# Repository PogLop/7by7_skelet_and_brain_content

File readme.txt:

in an unfinished state
wait for a few months 
please

thanks, 
sincerely,

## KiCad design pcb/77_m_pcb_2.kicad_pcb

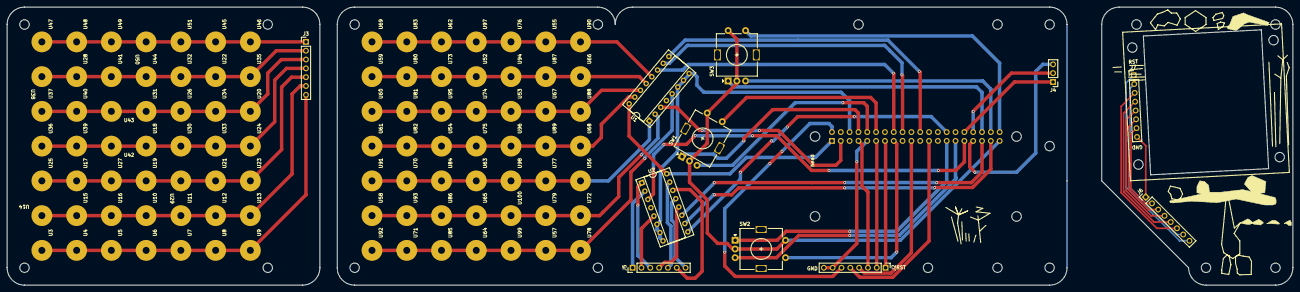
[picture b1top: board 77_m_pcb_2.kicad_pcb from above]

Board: 2 copper layers, 370.0 x 80.0 mm, 113 parts (0 on the bottom side), 59 nets.

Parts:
B1, B2, B3: Board
J1: Raspberry_Pi_2_3; Raspberry_Pi_Zero_Socketed_THT_FaceDown_MountingHoles
J2: Conn_01x08_Pin_nokia; PinHeader_1x08_P2.54mm_Vertical
J3, J5: Conn_01x07_Pin; PinHeader_1x07_P2.54mm_Vertical
J4: Conn_01x03_Pin; PinHeader_1x03_P2.54mm_Vertical
J6: Conn_01x08_Pin_nokia_balkon; PinHeader_1x08_P2.54mm_Vertical
J7: Conn_01x08_Pin_nokia_balkon_blizko; PinHeader_1x08_P2.54mm_Vertical
SW1, SW2, SW3: RotaryEncoder_Switch; RotaryEncoder_Alps_EC11E-Switch_Vertical_H20mm
U1, U2: 74HC4051; DIP-16_W7.62mm_Socket
U3, U4, U5, U6, U7, U8, U9, U10, U11, U12, U13, U14, U15, U16, U17, U18, U19, U20, U21, U22, U23, U24, U25, U26, U27, U28, U29, U30, U31, U32, U33, U34, U35, U36, U37, U38, U39, U40, U41, U42, U43, U44, U45, U46, U47, U48, U49, U50, U51, U52, U53, U54, U55, U56, U57, U58, U59, U60, U61, U62, U63, U64, U65, U66, U67, U68, U69, U70, U71, U72, U73, U74, U75, U76, U77, U78, U79, U80, U81, U82, U83, U84, U85, U86, U87, U88, U89, U90, U91, U92, U93, U94, U95, U96, U97, U98, U99, U100: 1x1_matrix_pin

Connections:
COM1: J1.3 (SDA/GPIO2), U1.3 (A)
COM2: J1.31 (GCLK2/GPIO6), U2.3 (A)
GND_PNUKY_ROT: J1.39 (GND), SW1.C, SW1.S2, SW2.C, SW2.S2, SW3.C, SW3.S2
KNOFL_A: J1.12 (GPIO18/PWM0), SW1.S1
KNOFL_B: J1.15 (GPIO22), SW2.S1
KNOFL_C: J1.40 (GPIO21/SCLK1), SW3.S1
NOK_BL: J1.9 (GND), J2.7, J2.8
NOK_CE: J1.11 (GPIO17), J2.2
NOK_CLK: J1.23 (SCLK0/GPIO11), J2.5
NOK_DC: J1.7 (GCLK0/GPIO4), J2.3
NOK_DIN: J1.19 (MOSI0/GPIO10), J2.4
NOK_RST: J1.13 (GPIO27), J2.1
NOK_VCC: J1.2 (5V), J2.6
unnamed: J3.1, U45.1, U46.1, U47.1, U48.1, U49.1, U50.1, U51.1
unnamed: J3.2, U22.1, U28.1, U32.1, U35.1, U38.1, U41.1, U44.1
unnamed: J3.3, U20.1, U26.1, U31.1, U34.1, U37.1, U40.1, U43.1
unnamed: J3.4, U18.1, U24.1, U30.1, U33.1, U36.1, U39.1, U42.1
unnamed: J3.5, U17.1, U19.1, U21.1, U23.1, U25.1, U27.1, U29.1
unnamed: J3.6, U10.1, U11.1, U12.1, U13.1, U14.1, U15.1, U16.1
unnamed: J3.7, U3.1, U4.1, U5.1, U6.1, U7.1, U8.1, U9.1
unnamed: J1.34 (GND), J4.2
unnamed: J5.1, U2.2 (A6)
unnamed: J5.2, U2.5 (A5)
unnamed: J5.3, U2.1 (A4)
unnamed: J5.4, U2.12 (A3)
unnamed: J5.5, U2.15 (A2)
unnamed: J5.6, U2.14 (A1)
unnamed: J5.7, U2.13 (A0)
unnamed: J6.1, J7.8
unnamed: J6.2, J7.7
unnamed: J6.3, J7.6
unnamed: J6.4, J7.5
unnamed: J6.5, J7.4
unnamed: J6.6, J7.3
unnamed: J6.7, J7.2
unnamed: J6.8, J7.1
unnamed: J1.6 (GND), U1.6 (~E), U1.7 (VEE), U1.8 (GND), U2.6 (~E), U2.7 (VEE), U2.8 (GND)
unnamed: J1.1 (3V3), U1.16 (VCC), U2.16 (VCC)
PNUK_A_GP_A: J1.8 (GPIO14/TXD), SW1.A
PNUK_A_GP_B: J1.10 (GPIO15/RXD), SW1.B
PNUK_B_GP_A: J1.27 (ID_SD/GPIO0), SW2.A
PNUK_B_GP_B: J1.29 (GCLK1/GPIO5), SW2.B
PNUK_C_GP_A: J1.36 (GPIO16), SW3.A
PNUK_C_GP_B: J1.38 (GPIO20/MOSI1), SW3.B
PWM_1_OUT: J1.32 (PWM0/GPIO12), J4.1
PWM_2_OUT: J1.33 (PWM1/GPIO13), J4.3
SEL0_A: J1.16 (GPIO23), U1.11 (S0)
SEL0_B: J1.35 (GPIO19/MISO1), U2.11 (S0)
SEL1_A: J1.18 (GPIO24), U1.10 (S1)
SEL1_B: J1.37 (GPIO26), U2.10 (S1)
SEL2_A: J1.22 (GPIO25), U1.9 (S2)
SEL2_B: J1.28 (ID_SC/GPIO1), U2.9 (S2)
m0: U1.13 (A0), U52.1, U59.1, U66.1, U73.1, U80.1, U87.1, U94.1
m1: U1.14 (A1), U53.1, U60.1, U67.1, U74.1, U81.1, U88.1, U95.1
m2: U1.15 (A2), U54.1, U61.1, U68.1, U75.1, U82.1, U89.1, U96.1
m3: U1.12 (A3), U55.1, U62.1, U69.1, U76.1, U83.1, U90.1, U97.1
m4: U1.1 (A4), U56.1, U63.1, U70.1, U77.1, U84.1, U91.1, U98.1
m5: U1.5 (A5), U57.1, U64.1, U71.1, U78.1, U85.1, U92.1, U99.1
m6: U1.2 (A6), U58.1, U65.1, U72.1, U79.1, U86.1, U93.1, U100.1

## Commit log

2025-12-23 ahooj
2025-12-23 neco se stalo
2025-12-23 dobrou
2025-12-26 vieo
2025-12-28 finally neco
2025-12-29 nokia nokia asi se rozbila
2025-12-29 nokia nokia asi se rozbila 2
2025-12-30 deda
2025-12-30 splachni dedu do zachodu - Official Manifest
2026-01-03 311218
2026-01-03 added note, pd and much more!
2026-01-26 opet neco mno!
2026-01-28 jejda
2026-01-28 plosny spoj na spojojuie
2026-01-28 experiment
2026-01-28 neplecha ukoncena
2026-01-31 random
2026-02-01 makefile !!!!! :))))
2026-02-04 neco se stalo zaszaszasz
2026-02-08 nedele
2026-02-11 streda
2026-02-12 konecne
2026-02-12 matrix blbne
2026-02-14 1234567890
2026-02-16 naive FUDI implemeted, untesdet
2026-02-16 foodis implementovan, asi facha
2026-02-17 konec miniosc.h, feet: refactoring trochu
2026-02-17 bugg
2026-02-17 hotovo pro dnesek
2026-02-24 nuudaa
2026-02-24 minor improvements finally backed-up config for fruit-puter turns out, that configuring pwm audio on pins 12 n 13 is not that hard, but whatever :O)
2026-03-01 config.h
2026-03-01 achichouvej
2026-03-02 feet: random
2026-03-03 gridlock.c refactoracie
2026-03-04 now using proper sip CE PCB has a mistake, im using gpio 2, that is hardwired to be always pullup but bodging the board didnt fix the matrix reading issue i dunno :o)
2026-03-04 pcb uklid, a tak
2026-03-06 juchu jupi simple_matrix~ konecne funguje!!! :o)
2026-03-09 vikend no
2026-03-10 pondeli (ted je utery)
2026-03-16 pondeli, mozna naposledy, rdousi mne to rmouceni, posledni
